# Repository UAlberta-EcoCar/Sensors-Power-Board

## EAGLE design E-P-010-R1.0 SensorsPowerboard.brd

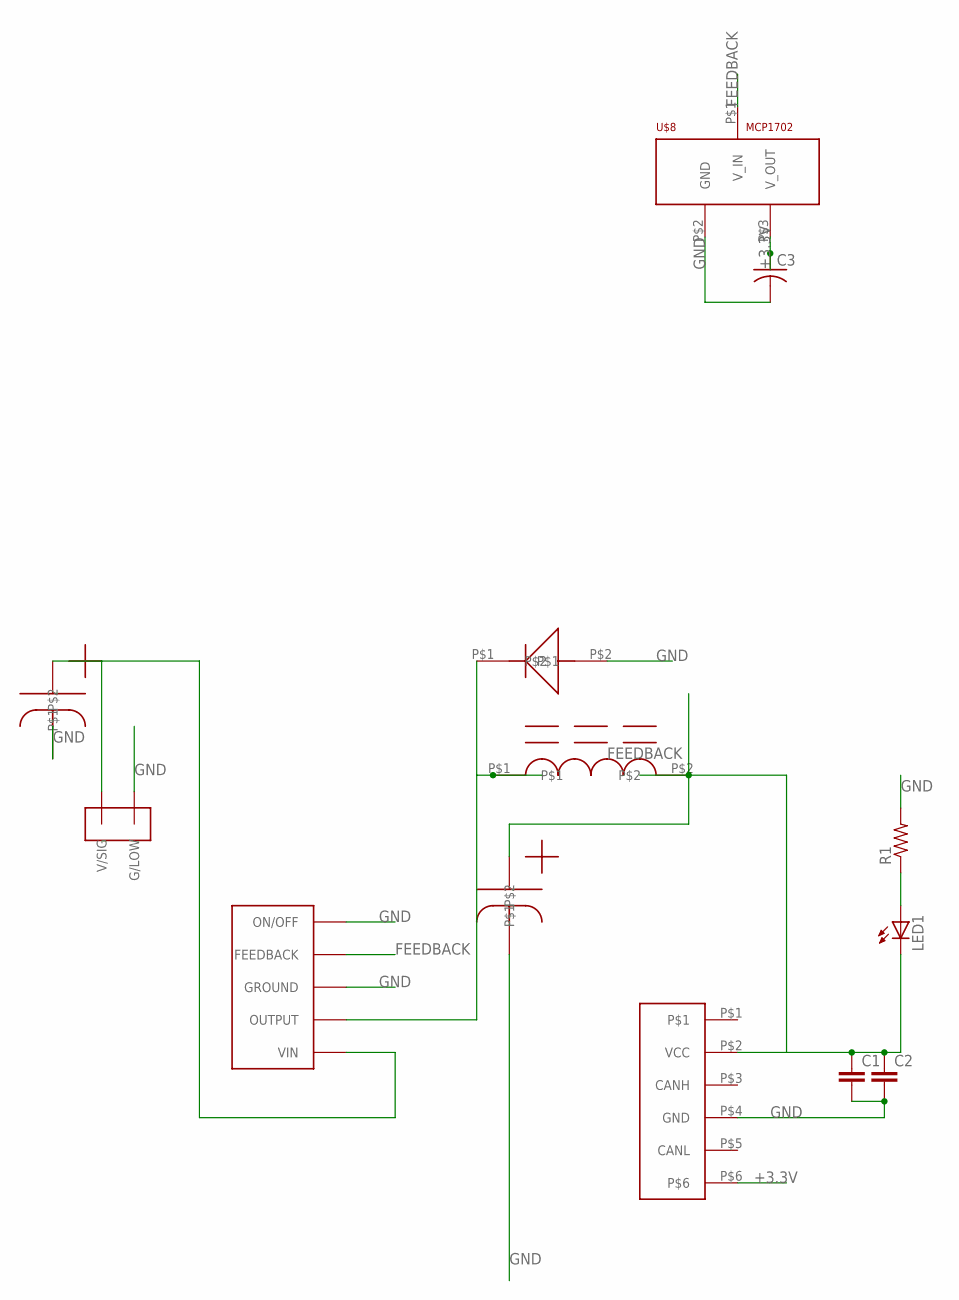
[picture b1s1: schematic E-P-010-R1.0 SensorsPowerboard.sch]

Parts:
C1, C2: CAP0805; 0805
C3: C-USC0805; C0805
LED1: LEDSMT1206; 1206
R1: RESISTOR0805-RES; 0805
U$1: LM2576; D2PAK-5
U$2: MBR360GOS
U$3: TE770966; 2X1-MATE-N-LOCK
U$4: CAN_6P6C
U$5: CAPESK107M025AC3AA; ESK107M025AC3AA
U$6: CAPESK108M025AH4EA; ESK108M025AH4EA
U$7: M1418-ND
U$8: MCP1702; SOT-23A

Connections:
+3.3V: C3.1, U$4.P$6, U$8.P$3 (V_OUT)
FEEDBACK: C1.1, C2.1, LED1.C, U$1.4 (FEEDBACK), U$4.P$2 (VCC), U$6.P$1, U$7.P$2, U$8.P$1 (V_IN)
GND: C1.2, C2.2, C3.2, R1.2, U$1.3 (GROUND), U$1.5 (ON/OFF), U$1.GROUND, U$2.P$2, U$3.CIRCUIT2 (G/LOW), U$4.P$4 (GND), U$5.P$2, U$6.P$2, U$8.P$2 (GND)
unnamed: U$1.2 (OUTPUT), U$2.P$1, U$7.P$1
unnamed: LED1.A, R1.1
V1: U$1.1 (VIN), U$3.CIRCUIT1 (V/SIG), U$5.P$1

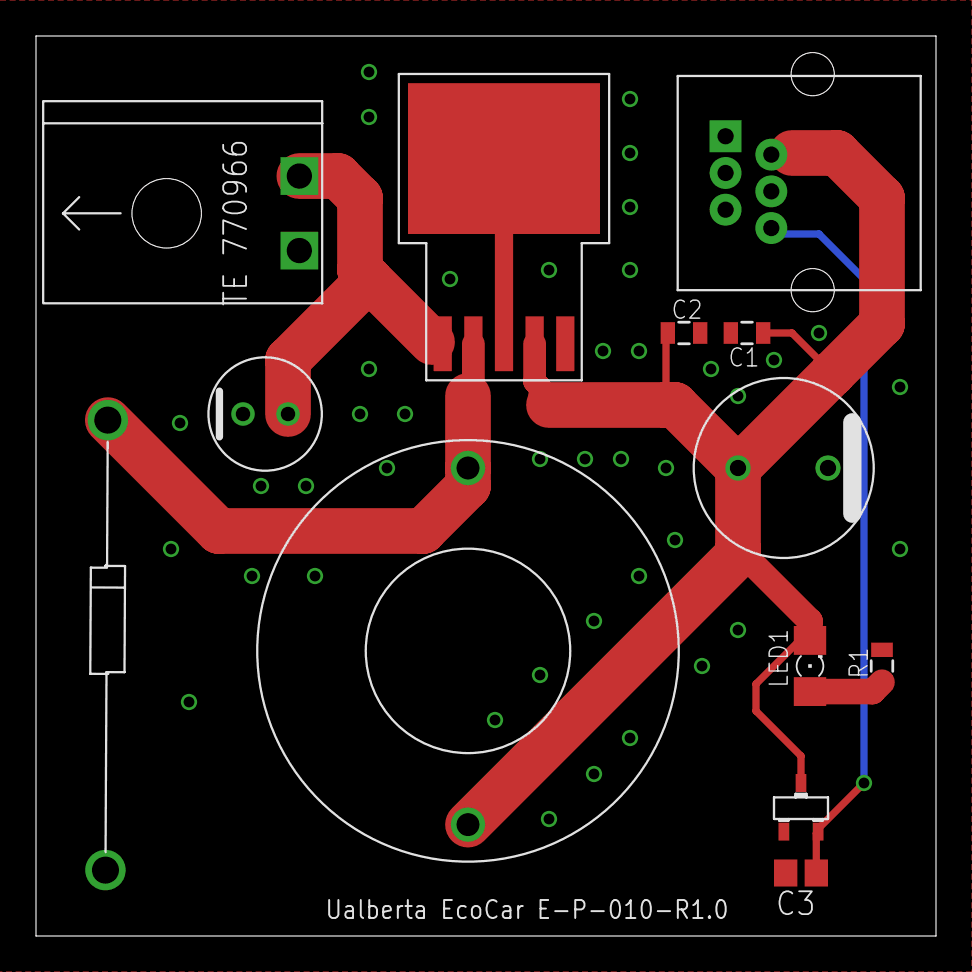
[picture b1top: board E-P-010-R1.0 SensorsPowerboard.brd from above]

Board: 2 copper layers, 50.0 x 50.0 mm, 13 parts (0 on the bottom side), 6 nets.

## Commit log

2016-01-23 Added eagle files
